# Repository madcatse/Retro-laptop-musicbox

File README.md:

# Retro-laptop-musicbox
 A stand-alone device that combines mt32-pi, LPT2MIDI and a COVOX

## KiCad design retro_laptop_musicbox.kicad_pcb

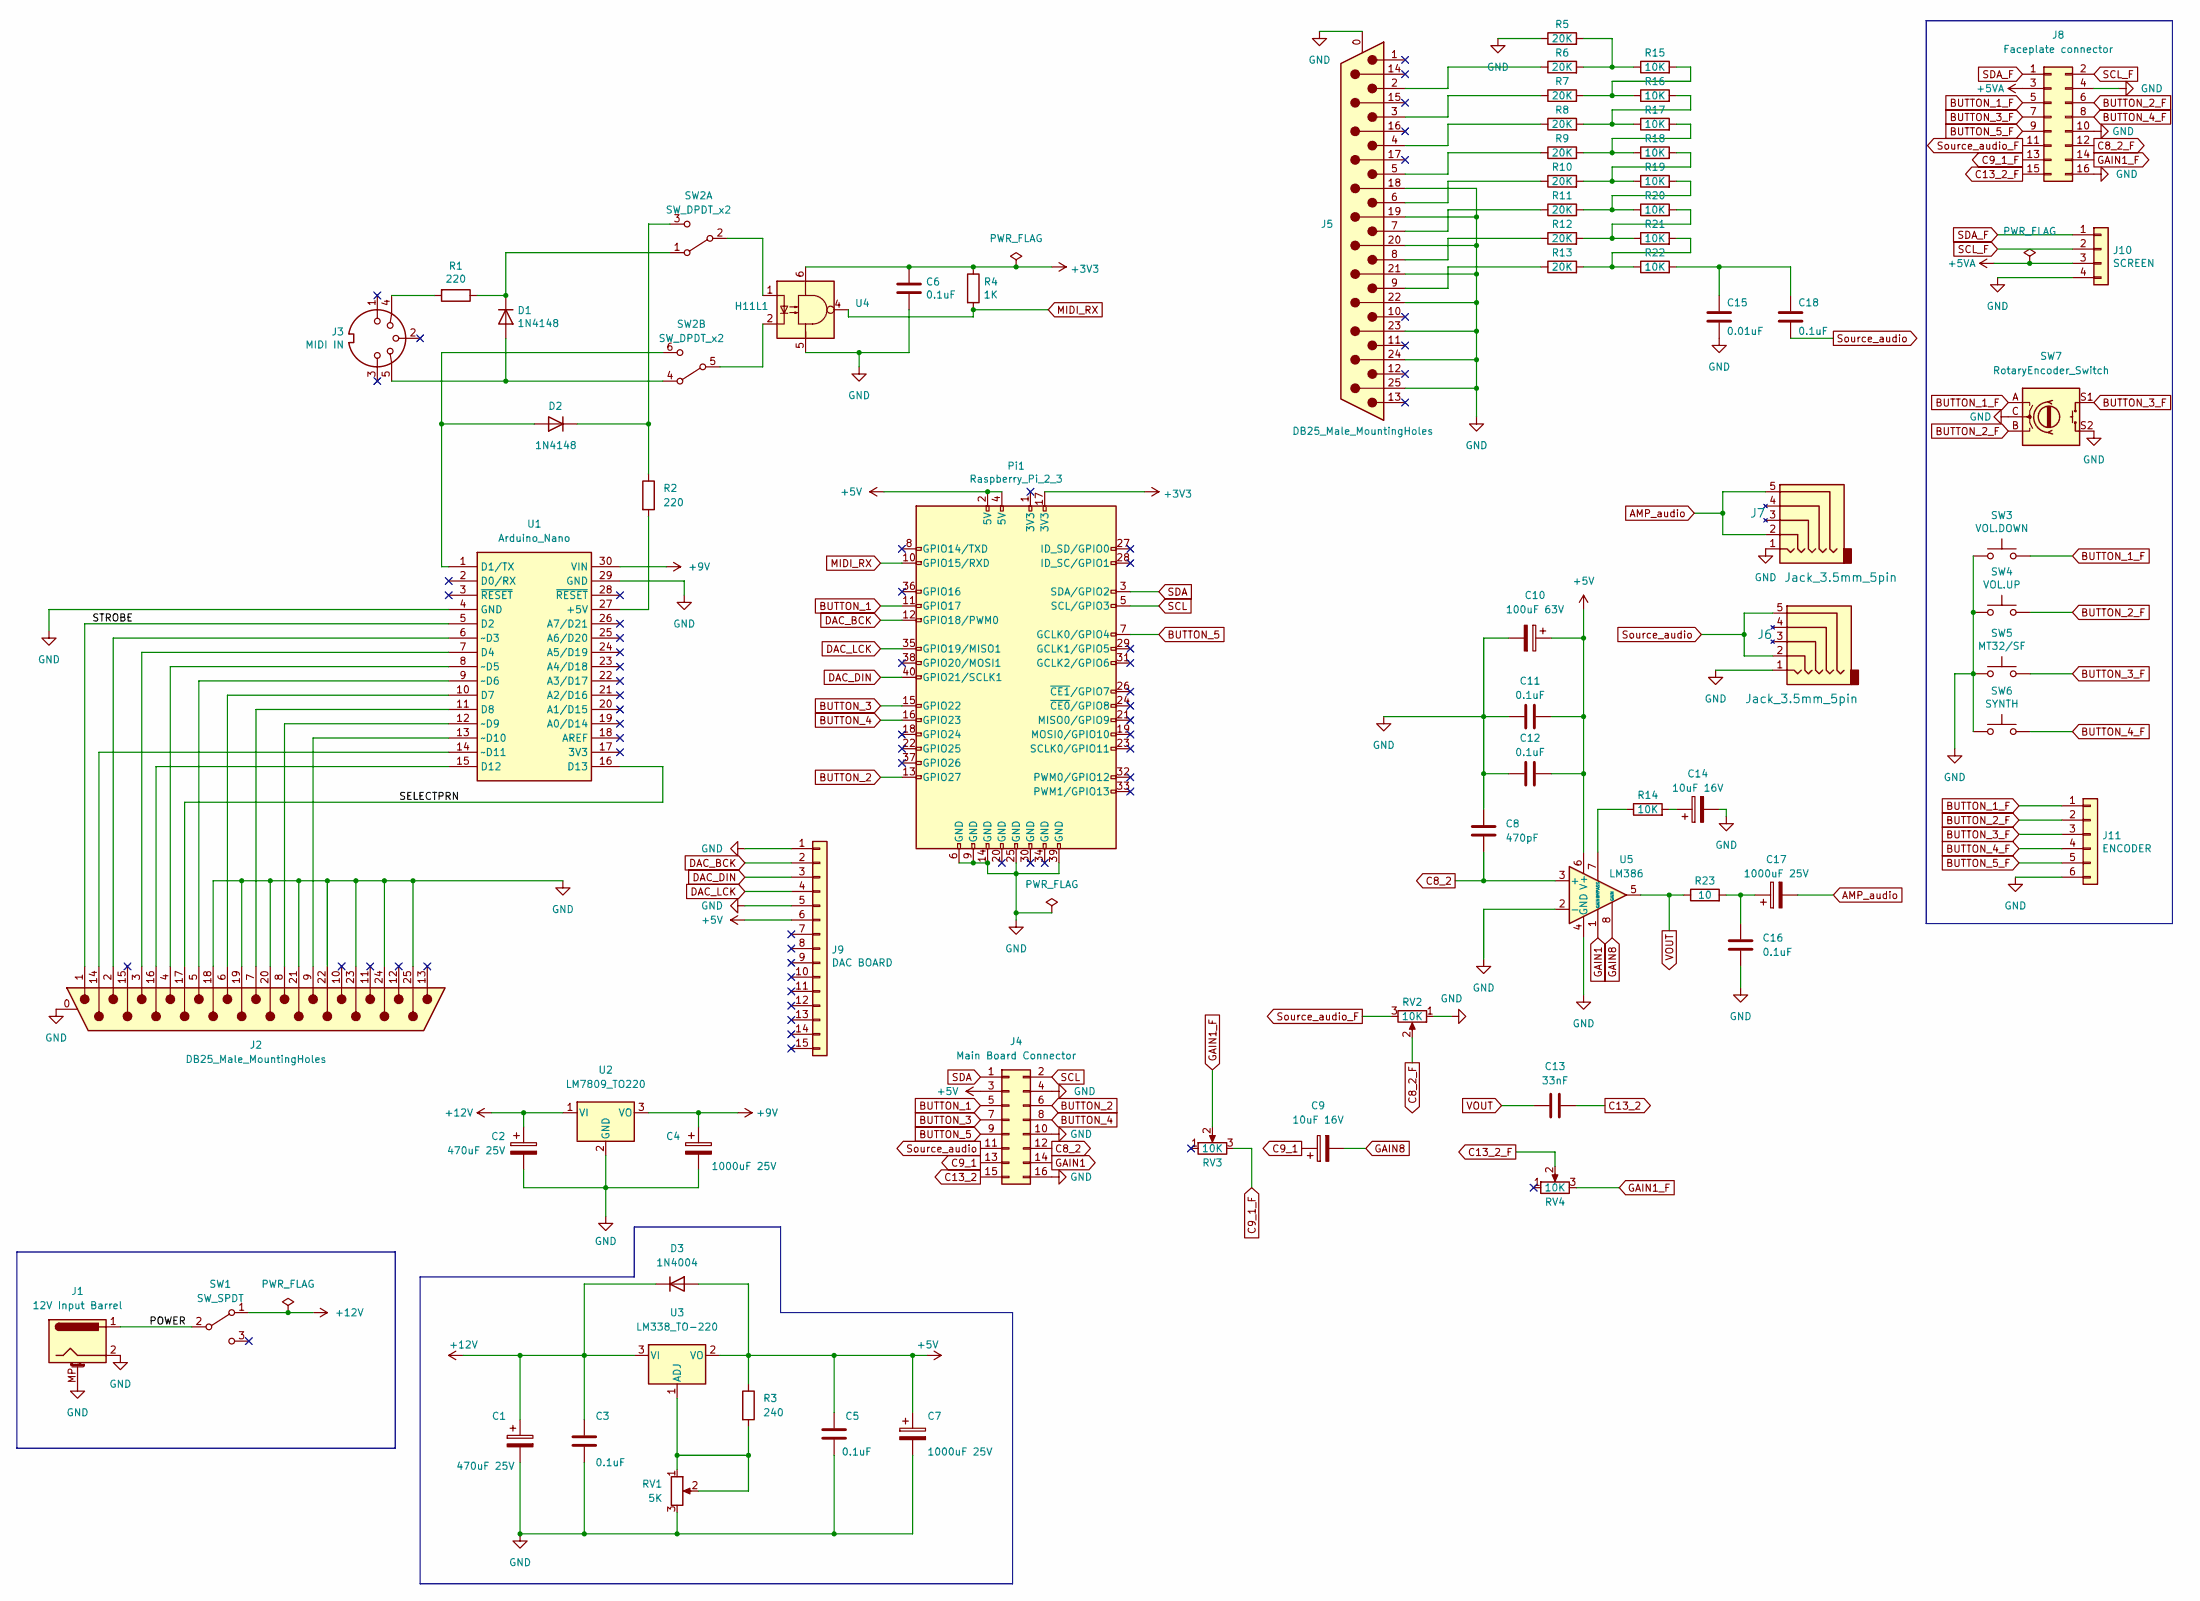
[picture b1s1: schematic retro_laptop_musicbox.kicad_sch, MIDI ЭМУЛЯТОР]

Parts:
C1, C2: 470uF 25V; CP_Radial_D10.0mm_P7.50mm
C3, C5, C6, C11, C12, C16, C18: 0.1uF; C_Disc_D4.7mm_W2.5mm_P5.00mm
C4, C7, C17: 1000uF 25V; CP_Radial_D10.0mm_P7.50mm
C8: 470pF; C_Disc_D4.7mm_W2.5mm_P5.00mm
C9, C14: 10uF 16V; CP_Radial_D5.0mm_P2.00mm
C10: 100uF 63V; CP_Radial_D10.0mm_P5.00mm
C13: 33nF; C_Disc_D4.7mm_W2.5mm_P5.00mm
C15: 0.01uF; C_Disc_D4.7mm_W2.5mm_P5.00mm
D1, D2: 1N4148; D_DO-35_SOD27_P7.62mm_Horizontal
D3: 1N4004; D_DO-41_SOD81_P10.16mm_Horizontal
J1: 12V Input Barrel; BarrelJack_GCT_DCJ200-10-A_Horizontal
J2, J5: DB25_Male_MountingHoles; DSUB-25_Male_Horizontal_P2.77x2.84mm_EdgePinOffset7.70mm_Ho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
J3: MIDI IN; DIN-5-Variable
J4: Main Board Connector; PinHeader_2x08_P2.54mm_Vertical
J6, J7: Jack_3.5mm_5pin; jack_5_pin_3f07_FINAL
J8: Faceplate connector; PinHeader_2x08_P2.54mm_Vertical
J9: DAC BOARD; PCM5102_full
J10: SCREEN; PinHeader_1x04_P2.54mm_Vertical
J11: ENCODER; PinHeader_1x06_P2.54mm_Vertical
Pi1: Raspberry_Pi_2_3; PinHeader_2x20_P2.54mm_Vertical
R1, R2: 220; R_Axial_DIN0207_L6.3mm_D2.5mm_P10.16mm_Horizontal
R3: 240; R_Axial_DIN0207_L6.3mm_D2.5mm_P10.16mm_Horizontal
R4: 1K; R_Axial_DIN0207_L6.3mm_D2.5mm_P10.16mm_Horizontal
R5, R6, R7, R8, R9, R10, R11, R12, R13: 20K; R_Axial_DIN0207_L6.3mm_D2.5mm_P10.16mm_Horizontal
R14, R15, R16, R17, R18, R19, R20, R21, R22: 10K; R_Axial_DIN0207_L6.3mm_D2.5mm_P10.16mm_Horizontal
R23: 10; R_Axial_DIN0207_L6.3mm_D2.5mm_P10.16mm_Horizontal
RV1: 5K; Potentiometer_Runtron_RM-065_Vertical
RV2, RV3, RV4: 10K; Potentiometer_Alpha_RD901F-40-00D_Single_Vertical_CircularH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
SW1: SW_SPDT; MTS-102-C3
SW2: SW_DPDT_x2; SW_CuK_JS202011AQN_DPDT_Angled2
SW3: VOL.DOWN; SW_PUSH_6mm
SW4: VOL.UP; SW_PUSH_6mm
SW5: MT32/SF; SW_PUSH_6mm
SW6: SYNTH; SW_PUSH_6mm
SW7: RotaryEncoder_Switch; RotaryEncoder_Alps_EC11E-Switch_Vertical_H20mm
U1: Arduino_Nano
U2: LM7809_TO220; TO-220-3_Vertical
U3: LM338_TO-220; TO-220-3_Vertical
U4: H11L1; DIP-6_W7.62mm
U5: LM386; DIP-8_W7.62mm

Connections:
+3V3: C6.1, Pi1.17 (3V3), R4.1, U4.6
+5V: C5.1, C7.1, C10.1, C11.2, C12.2, D3.2 (A), J4.3, J9.6, Pi1.2 (5V), Pi1.4 (5V), R3.1, U3.2 (VO), U5.6 (V+)
+5VA: J8.3, J10.3
+9V: C4.1, U1.30 (VIN), U2.3 (VO)
+12V: C1.1, C2.1, C3.1, D3.1 (K), SW1.1 (A), U2.1 (VI), U3.3 (VI)
/POWER: J1.1, SW1.2 (B)
/SELECTPRN: J2.17, U1.16 (D13)
/STROBE: J2.1, U1.5 (D2)
AMP_audio: C17.2, J7.2, J7.5
BUTTON_1: J4.5, Pi1.11 (GPIO17)
BUTTON_1_F: J8.5, J11.1, SW3.2, SW7.A
BUTTON_2: J4.6, Pi1.13 (GPIO27)
BUTTON_2_F: J8.6, J11.2, SW4.2, SW7.B
BUTTON_3: J4.7, Pi1.15 (GPIO22)
BUTTON_3_F: J8.7, J11.3, SW5.2, SW7.S1
BUTTON_4: J4.8, Pi1.16 (GPIO23)
BUTTON_4_F: J8.8, J11.4, SW6.2
BUTTON_5: J4.9, Pi1.7 (GCLK0/GPIO4)
BUTTON_5_F: J8.9, J11.5
C8_2: C8.2, J4.12, U5.3 (+)
C8_2_F: J8.12, RV2.2
C9_1: C9.1, J4.13
C9_1_F: J8.13, RV3.3
C13_2: C13.2, J4.15
C13_2_F: J8.15, RV4.2
DAC_BCK: J9.2, Pi1.12 (GPIO18/PWM0)
DAC_DIN: J9.3, Pi1.40 (GPIO21/SCLK1)
DAC_LCK: J9.4, Pi1.35 (GPIO19/MISO1)
GAIN1: J4.14, U5.1 (GAIN)
GAIN1_F: J8.14, RV3.2, RV4.3
GAIN8: C9.2, U5.8 (GAIN)
GND: C1.2, C2.2, C3.2, C4.2, C5.2, C6.2, C7.2, C8.1, C10.2, C11.1, C12.1, C14.2, C15.2, C16.2, J1.2, J1.MP (MountPin), J2.0 (PAD), J2.18, J2.19, J2.20, J2.21, J2.22, J2.23, J2.24, J2.25, J4.4, J4.10, J4.16, J5.0 (PAD), J5.18, J5.19, J5.20, J5.21, J5.22, J5.23, J5.24, J5.25, J6.1, J7.1, J8.4, J8.10, J8.16, J9.1, J9.5, J10.4, J11.6, Pi1.6 (GND), Pi1.9 (GND), Pi1.14 (GND), Pi1.25 (GND), Pi1.39 (GND), R5.1, RV1.3, RV2.1, SW7.C, SW7.S2, U1.4 (GND), U1.29 (GND), U2.2 (GND), U4.5, U5.2 (-), U5.4 (GND)
MIDI_RX: Pi1.10 (GPIO15/RXD), R4.2, U4.4
unnamed: C14.1, R14.2
unnamed: C15.1, C18.1, R22.2
unnamed: C16.1, C17.1, R23.2
unnamed: D1.1 (K), R1.1, SW2.1 (A)
unnamed: D1.2 (A), J3.5, SW2.4 (A)
unnamed: D2.1 (K), R2.1, SW2.3 (C)
unnamed: D2.2 (A), SW2.6 (C), U1.1 (D1/TX)
unnamed: J2.2, U1.6 (~D3)
unnamed: J2.3, U1.7 (D4)
unnamed: J2.4, U1.8 (~D5)
unnamed: J2.5, U1.9 (~D6)
unnamed: J2.6, U1.10 (D7)
unnamed: J2.7, U1.11 (D8)
unnamed: J2.8, U1.12 (~D9)
unnamed: J2.9, U1.13 (~D10)
unnamed: J2.14, U1.14 (~D11)
unnamed: J2.16, U1.15 (D12)
unnamed: J3.4, R1.2
unnamed: J5.2, R6.1
unnamed: J5.3, R7.1
unnamed: J5.4, R8.1
unnamed: J5.5, R9.1
unnamed: J5.6, R10.1
unnamed: J5.7, R11.1
unnamed: J5.8, R12.1
unnamed: J5.9, R13.1
unnamed: R2.2, U1.27 (+5V)
unnamed: R3.2, RV1.1, RV1.2, U3.1 (ADJ)
unnamed: R10.2, R18.2, R19.1
unnamed: R11.2, R19.2, R20.1
unnamed: R12.2, R20.2, R21.1
unnamed: R13.2, R21.2, R22.1
unnamed: R14.1, U5.7 (BYPASS)
unnamed: R5.2, R6.2, R15.1
unnamed: R7.2, R15.2, R16.1
unnamed: R8.2, R16.2, R17.1
unnamed: R9.2, R17.2, R18.1
unnamed: SW2.2 (B), U4.1
unnamed: SW2.5 (B), U4.2
unnamed: SW3.1, SW4.1, SW5.1, SW6.1
SCL: J4.2, Pi1.5 (SCL/GPIO3)
SCL_F: J8.2, J10.2
SDA: J4.1, Pi1.3 (SDA/GPIO2)
SDA_F: J8.1, J10.1
Source_audio: C18.2, J4.11, J6.2, J6.5
Source_audio_F: J8.11, RV2.3
VOUT: C13.1, R23.1, U5.5

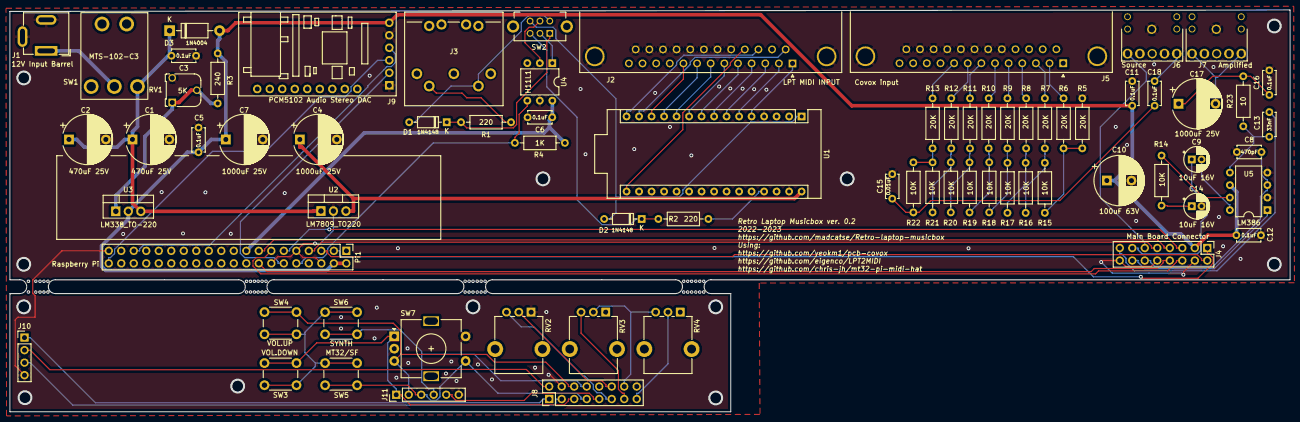
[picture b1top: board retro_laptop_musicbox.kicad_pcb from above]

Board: 2 copper layers, 260.0 x 81.6 mm, 80 parts (0 on the bottom side), 80 nets.

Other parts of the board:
mouse-bite-2.54mm-slot_1, mouse-bite-2.54mm-slot_2, mouse-bite-2.54mm-slot_5, mouse-bite-2.54mm-slot_6, mouse-bite-2.54mm-slot_9, mouse-bite-2.54mm-slot_10, mouse-bite-2.54mm-slot_13, mouse-bite-2.54mm-slot_14: VAL**; mouse-bite-2.54mm-slot

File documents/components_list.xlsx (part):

Source: | C:\KICAD\projects\my_pcb\my_pcb.kicad_sch
Date: | 44993.738599537035
Tool: | Eeschema (6.0.10)
Generator: | C:\Program Files\KiCad\6.0\bin\scripting\plugins/bom_csv_grouped_by_value.py
Component Count: | 72.0
Individual Components:
Item | Qty | Reference(s) | Value | LibPart | Footprint | Datasheet | Название
 |  | C1 | 470uF 25V | Device:C_Polarized | Capacitor_THT:CP_Radial_D10.0mm_P7.50mm | ~ | ECAP (К50-35), 470 мкФ, 25 В, 105°C, 10x12,5, B41851F5477M000, Конденсатор элек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
 |  | C2 | 470uF 25V | Device:C_Polarized | Capacitor_THT:CP_Radial_D10.0mm_P7.50mm | ~ | ECAP (К50-35), 470 мкФ, 25 В, 105°C, 10x12,5, B41851F5477M000, Конденсатор элек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
 |  | C3 | 0.1uF | Device:C | Capacitor_THT:C_Disc_D4.7mm_W2.5mm_P5.00mm | https://static.chipdip.ru/lib/056/DOC000056282.pdf | К10-17Б 0.1 мкФ X7R,10%, 0805, Конденсатор керамический выводной
 |  | C4 | 1000uF 25V | Device:C_Polarized | Capacitor_THT:CP_Radial_D10.0mm_P7.50mm | ~ | ECAP (К50-35), 1000 мкФ, 25 В, 105°C, 10x20, B41851A5108M000, Конденсатор элект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
 |  | C5 | 0.1uF | Device:C | Capacitor_THT:C_Disc_D4.7mm_W2.5mm_P5.00mm | https://static.chipdip.ru/lib/056/DOC000056282.pdf | К10-17Б 0.1 мкФ X7R,10%, 0805, Конденсатор керамический выводной
 |  | C6 | 0.1uF | Device:C | Capacitor_THT:C_Disc_D4.7mm_W2.5mm_P5.00mm | https://static.chipdip.ru/lib/056/DOC000056282.pdf | К10-17Б 0.1 мкФ X7R,10%, 0805, Конденсатор керамический выводной
 |  | C7 | 1000uF 25V | Device:C_Polarized | Capacitor_THT:CP_Radial_D10.0mm_P7.50mm | ~ | ECAP (К50-35), 1000 мкФ, 25 В, 105°C, 10x20, B41851A5108M000, Конденсатор элект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
 |  | C8 | 470pF | Device:C | Capacitor_THT:C_Disc_D4.7mm_W2.5mm_P5.00mm | https://static.chipdip.ru/lib/056/DOC000056282.pdf | К10-17Б 470пФ NPO,5%,0805, Конденсатор керамический выводной
 |  | C9 | 10uF 16V | Device:C_Polarized | Capacitor_THT:CP_Radial_D5.0mm_P2.00mm | https://static.chipdip.ru/lib/279/DOC000279577.pdf | ECAP (К50-35), 10мкФ, 16В, 105°C, 20%, 5x11мм P:2мм, Конденсатор электролитичес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
 |  | C10 | 100uF 63V | Device:C_Polarized | Capacitor_THT:CP_Radial_D10.0mm_P5.00mm | https://static.chipdip.ru/lib/279/DOC000279577.pdf | ECAP (К50-35), 100мкФ, 63В, 105°C, 20%, 10x12мм P:5мм, Конденсатор электролитич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
 |  | C11 | 0.1uF | Device:C | Capacitor_THT:C_Disc_D4.7mm_W2.5mm_P5.00mm | https://static.chipdip.ru/lib/056/DOC000056282.pdf | К10-17Б 0.1 мкФ X7R,10%, 0805, Конденсатор керамический выводной
 |  | C12 | 0.1uF | Device:C | Capacitor_THT:C_Disc_D4.7mm_W2.5mm_P5.00mm | https://static.chipdip.ru/lib/056/DOC000056282.pdf | К10-17Б 0.1 мкФ X7R,10%, 0805, Конденсатор керамический выводной
 |  | C13 | 33nF | Device:C | Capacitor_THT:C_Disc_D4.7mm_W2.5mm_P5.00mm | https://static.chipdip.ru/lib/056/DOC000056282.pdf | К10-17Б 0.033мкФ X7R,10%,0805, Конденсатор керамический выводной
 |  | C14 | 10uF 16V | Device:C_Polarized | Capacitor_THT:CP_Radial_D5.0mm_P2.00mm | https://static.chipdip.ru/lib/279/DOC000279577.pdf | ECAP (К50-35), 10мкФ, 16В, 105°C, 20%, 5x11мм P:2мм, Конденсатор электролитичес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
 |  | C15 | 0.01uF | Device:C | Capacitor_THT:C_Disc_D4.7mm_W2.5mm_P5.00mm | https://static.chipdip.ru/lib/056/DOC000056282.pdf | К10-17Б 0.01 мкФ X7R,10%,0805, Конденсатор керамический выводной
 |  | C16 | 0.1uF | Device:C | Capacitor_THT:C_Disc_D4.7mm_W2.5mm_P5.00mm | https://static.chipdip.ru/lib/056/DOC000056282.pdf | К10-17Б 0.1 мкФ X7R,10%, 0805, Конденсатор керамический выводной
 |  | C17 | 1000uF 25V | Device:C_Polarized | Capacitor_THT:CP_Radial_D10.0mm_P7.50mm | ~ | ECAP (К50-35), 1000 мкФ, 25 В, 105°C, 10x20, B41851A5108M000, Конденсатор элект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
 |  | C18 | 0.1uF | Device:C | Capacitor_THT:C_Disc_D4.7mm_W2.5mm_P5.00mm | https://static.chipdip.ru/lib/056/DOC000056282.pdf | К10-17Б 0.1 мкФ X7R,10%, 0805, Конденсатор керамический выводной
 |  | D1 | 1N4148 | Diode:1N4148 | Diode_THT:D_DO-35_SOD27_P7.62mm_Horizontal | https://static.chipdip.ru/lib/007/DOC003007981.pdf | 1N4148, Диод 150мА 100В [DO-35]
 |  | D2 | 1N4148 | Diode:1N4148 | Diode_THT:D_DO-35_SOD27_P7.62mm_Horizontal | https://static.chipdip.ru/lib/007/DOC003007981.pdf | 1N4148, Диод 150мА 100В [DO-35]
 |  | D3 | 1N4004 | Diode:1N4004 | Diode_THT:D_DO-41_SOD81_P10.16mm_Horizontal | http://www.vishay.com/docs/88503/1n4001.pdf | 1N4004, Диод выпрямительный 1А 400В [DO-41]
 |  | J1 | 12V Input Barrel | Connector:Barrel_Jack_MountingPin | w_conn_av:BarrelJack_GCT_DCJ200-10-A_Horizontal | https://static.chipdip.ru/lib/485/DOC014485047.pdf | DJK-02A (L-KLS1-DC-005A-2.0), Гнездо питания на плату 2,0х9мм
 |  | J2 | DB25_Male_MountingHoles | Connector:DB25_Male_MountingHoles | Connector_Dsub:DSUB-25_Male_Horizontal_P2.77x2.84mm_EdgePinOffset7.70mm_Housed_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 | https://static.chipdip.ru/lib/584/DOC000584749.pdf | DRB-25MA разъем типа D-SAB серии DRB, M-вилка угловая
 |  | J3 | MIDI IN | Connector:DIN-5_180degree | w_conn_av:DIN-5-Variable | http://www.mouser.com/ds/2/18/40_c091_abd_e-75918.pdf | Разъем DIN 5HP[45] розетка, на блок, GM-545-4
 |  | J4 | Main Board Connector | Connector_Generic:Conn_02x08_Odd_Even | Connector_PinHeader_2.54mm:PinHeader_2x08_P2.54mm_Vertical | ~
 |  | J5 | DB25_Male_MountingHoles | Connector:DB25_Male_MountingHoles | Connector_Dsub:DSUB-25_Male_Horizontal_P2.77x2.84mm_EdgePinOffset7.70mm_Housed_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 | https://static.chipdip.ru/lib/584/DOC000584749.pdf | DRB-25MA разъем типа D-SAB серии DRB, M-вилка угловая
 |  | J6 | Jack_3.5mm_5pin | w_connectors:AudioJack_5_pin | w_conn_av:jack_5_pin_3f07_FINAL |  | CKX3-3.5-06 гнездо на плату
 |  | J7 | Jack_3.5mm_5pin | w_connectors:AudioJack_5_pin | w_conn_av:jack_5_pin_3f07_FINAL |  | CKX3-3.5-06 гнездо на плату
 |  | J8 | Faceplate connector | Connector_Generic:Conn_02x08_Odd_Even | Connector_PinHeader_2.54mm:PinHeader_2x08_P2.54mm_Vertical | ~
 |  | J9 | DAC BOARD | Connector_Generic:Conn_01x15 | w_conn_av:PCM5102_full | ~ | Интерфейс I2S PCM5102A DAC декодер
 |  | J10 | SCREEN | Connector_Generic:Conn_01x04 | Connector_PinHeader_2.54mm:PinHeader_1x04_P2.54mm_Vertical | ~ | PBS-4 (DS-1023 - 1x4), Гнездо на плату 2.54мм 1х4pin прямое
 |  | J11 | ENCODER | Connector_Generic:Conn_01x06 | Connector_PinHeader_2.54mm:PinHeader_1x06_P2.54mm_Vertical | ~ | PLS-6 (DS1021-1*6SF112), Вилка штыревая 2.54мм 1x6pin прямая тип12
 |  | Pi1 | Raspberry_Pi_2_3 | Connector:Raspberry_Pi_2_3 | Connector_PinHeader_2.54mm:PinHeader_2x20_P2.54mm_Vertical | https://www.raspberrypi.org/documentation/hardware/raspberry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 | PBD-40 (DS1023-2X20), Гнездо на плату 2.54мм 2х20pin прямое
 |  | R1 | 220.0 | Device:R | Resistor_THT:R_Axial_DIN0207_L6.3mm_D2.5mm_P10.16mm_Horizontal | ~ | MF-25 (С2-23) 0.25 Вт, 220 Ом, 1%, Резистор металлопленочный
 |  | R2 | 220.0 | Device:R | Resistor_THT:R_Axial_DIN0207_L6.3mm_D2.5mm_P10.16mm_Horizontal | ~ | MF-25 (С2-23) 0.25 Вт, 220 Ом, 1%, Резистор металлопленочный
 |  | R3 | 240.0 | Device:R | Resistor_THT:R_Axial_DIN0207_L6.3mm_D2.5mm_P10.16mm_Horizontal | ~ | MF-25 (С2-23) 0.25 Вт, 240 Ом, 1%, Резистор металлопленочный
 |  | R4 | 1K | Device:R | Resistor_THT:R_Axial_DIN0207_L6.3mm_D2.5mm_P10.16mm_Horizontal | ~ | MF-25 (С2-23) 0.25 Вт, 1 кОм, 1%, Резистор металлопленочный
 |  | R5 | 20K | Device:R | Resistor_THT:R_Axial_DIN0207_L6.3mm_D2.5mm_P10.16mm_Horizontal | ~ | MF-25 (С2-23) 0.25 Вт, 20 кОм, 1%, Резистор металлопленочный
 |  | R6 | 20K | Device:R | Resistor_THT:R_Axial_DIN0207_L6.3mm_D2.5mm_P10.16mm_Horizontal | ~ | MF-25 (С2-23) 0.25 Вт, 20 кОм, 1%, Резистор металлопленочный
 |  | R7 | 20K | Device:R | Resistor_THT:R_Axial_DIN0207_L6.3mm_D2.5mm_P10.16mm_Horizontal | ~ | MF-25 (С2-23) 0.25 Вт, 20 кОм, 1%, Резистор металлопленочный
 |  | R8 | 20K | Device:R | Resistor_THT:R_Axial_DIN0207_L6.3mm_D2.5mm_P10.16mm_Horizontal | ~ | MF-25 (С2-23) 0.25 Вт, 20 кОм, 1%, Резистор металлопленочный
 |  | R9 | 20K | Device:R | Resistor_THT:R_Axial_DIN0207_L6.3mm_D2.5mm_P10.16mm_Horizontal | ~ | MF-25 (С2-23) 0.25 Вт, 20 кОм, 1%, Резистор металлопленочный
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
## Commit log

2023-03-17 Version 0.2
    Version 0.2
2023-03-17 New gerbers
2023-03-24 March 24 update
2023-03-26 March 26th Update
2023-05-31 Update sym-lib-table
2023-06-03 Update June 2023
2023-07-18 Update 19072023
2023-10-31 3d stuff
2026-05-26 Cleanup
2026-05-26 Update Kicad 10
